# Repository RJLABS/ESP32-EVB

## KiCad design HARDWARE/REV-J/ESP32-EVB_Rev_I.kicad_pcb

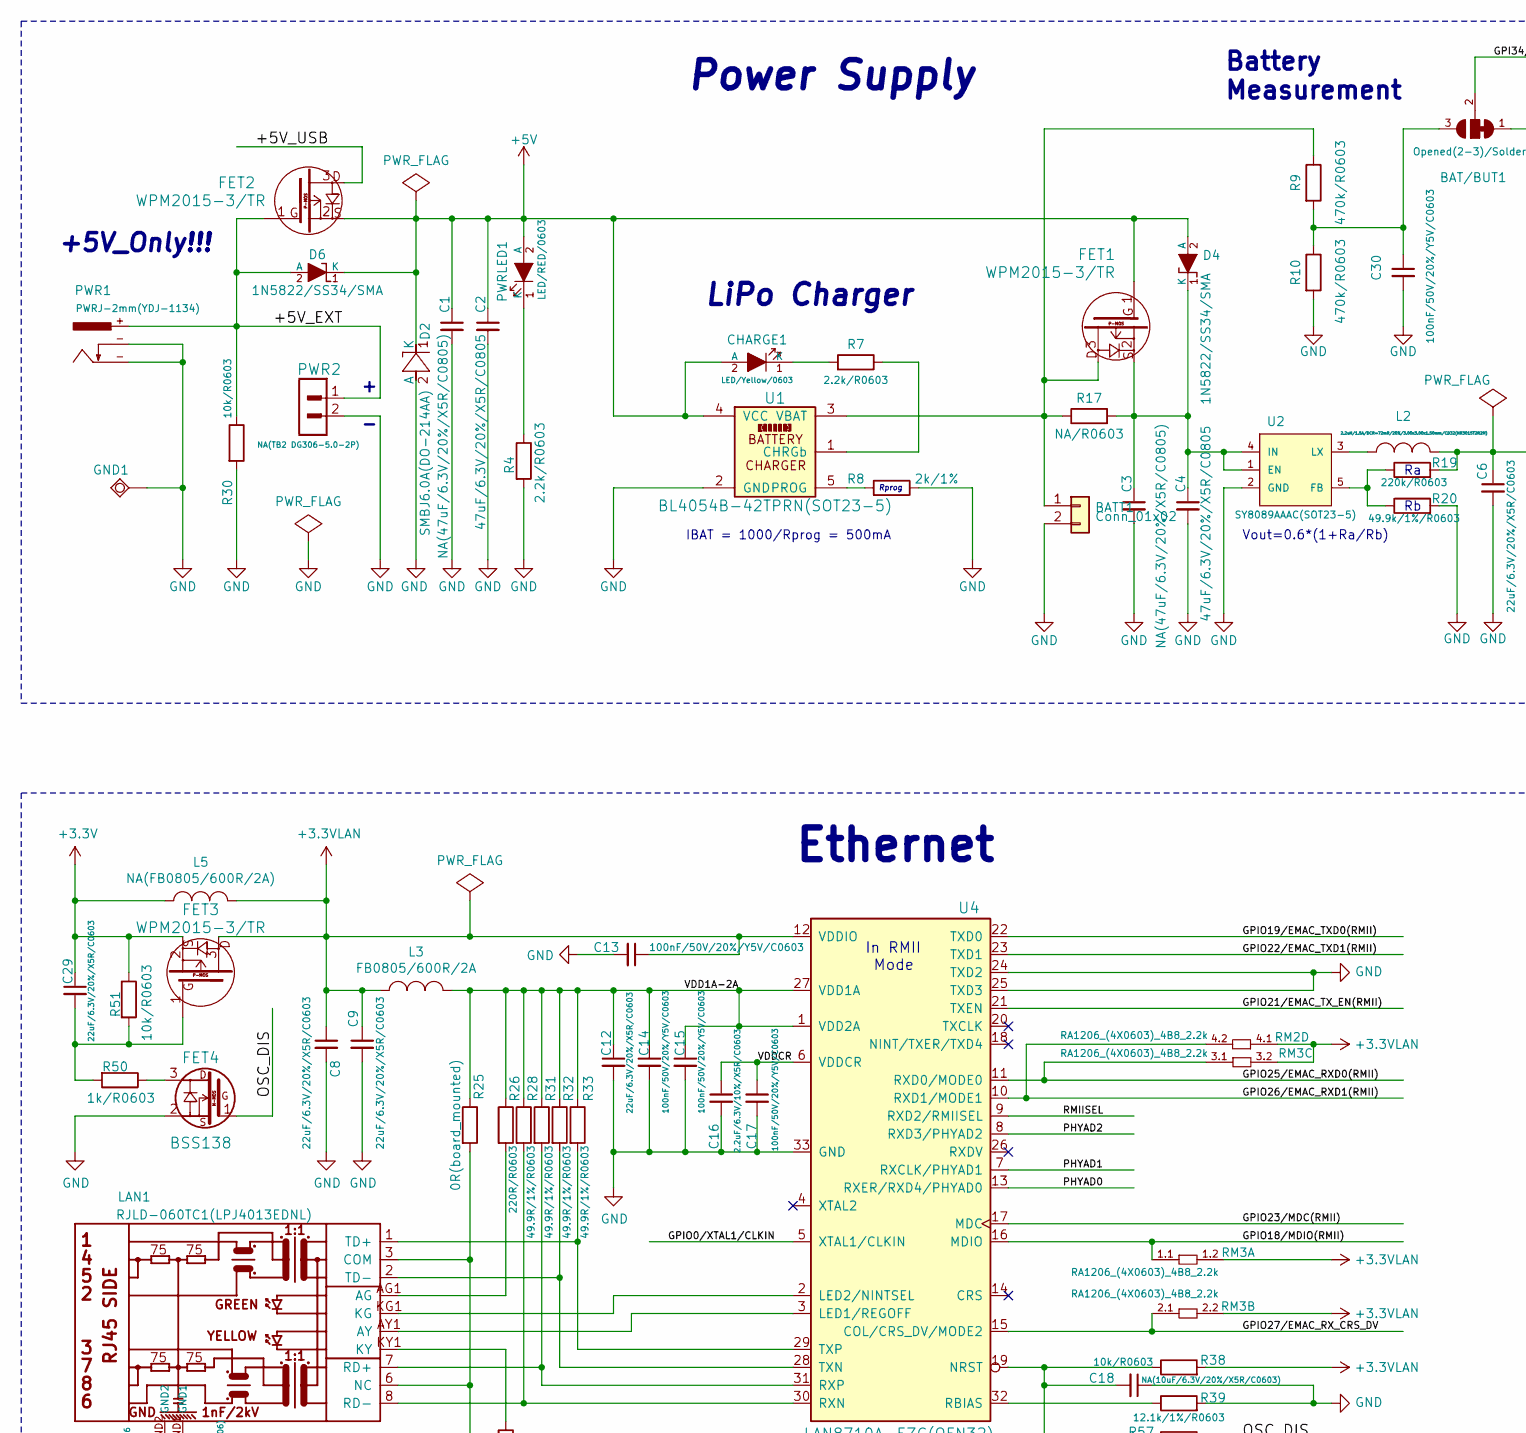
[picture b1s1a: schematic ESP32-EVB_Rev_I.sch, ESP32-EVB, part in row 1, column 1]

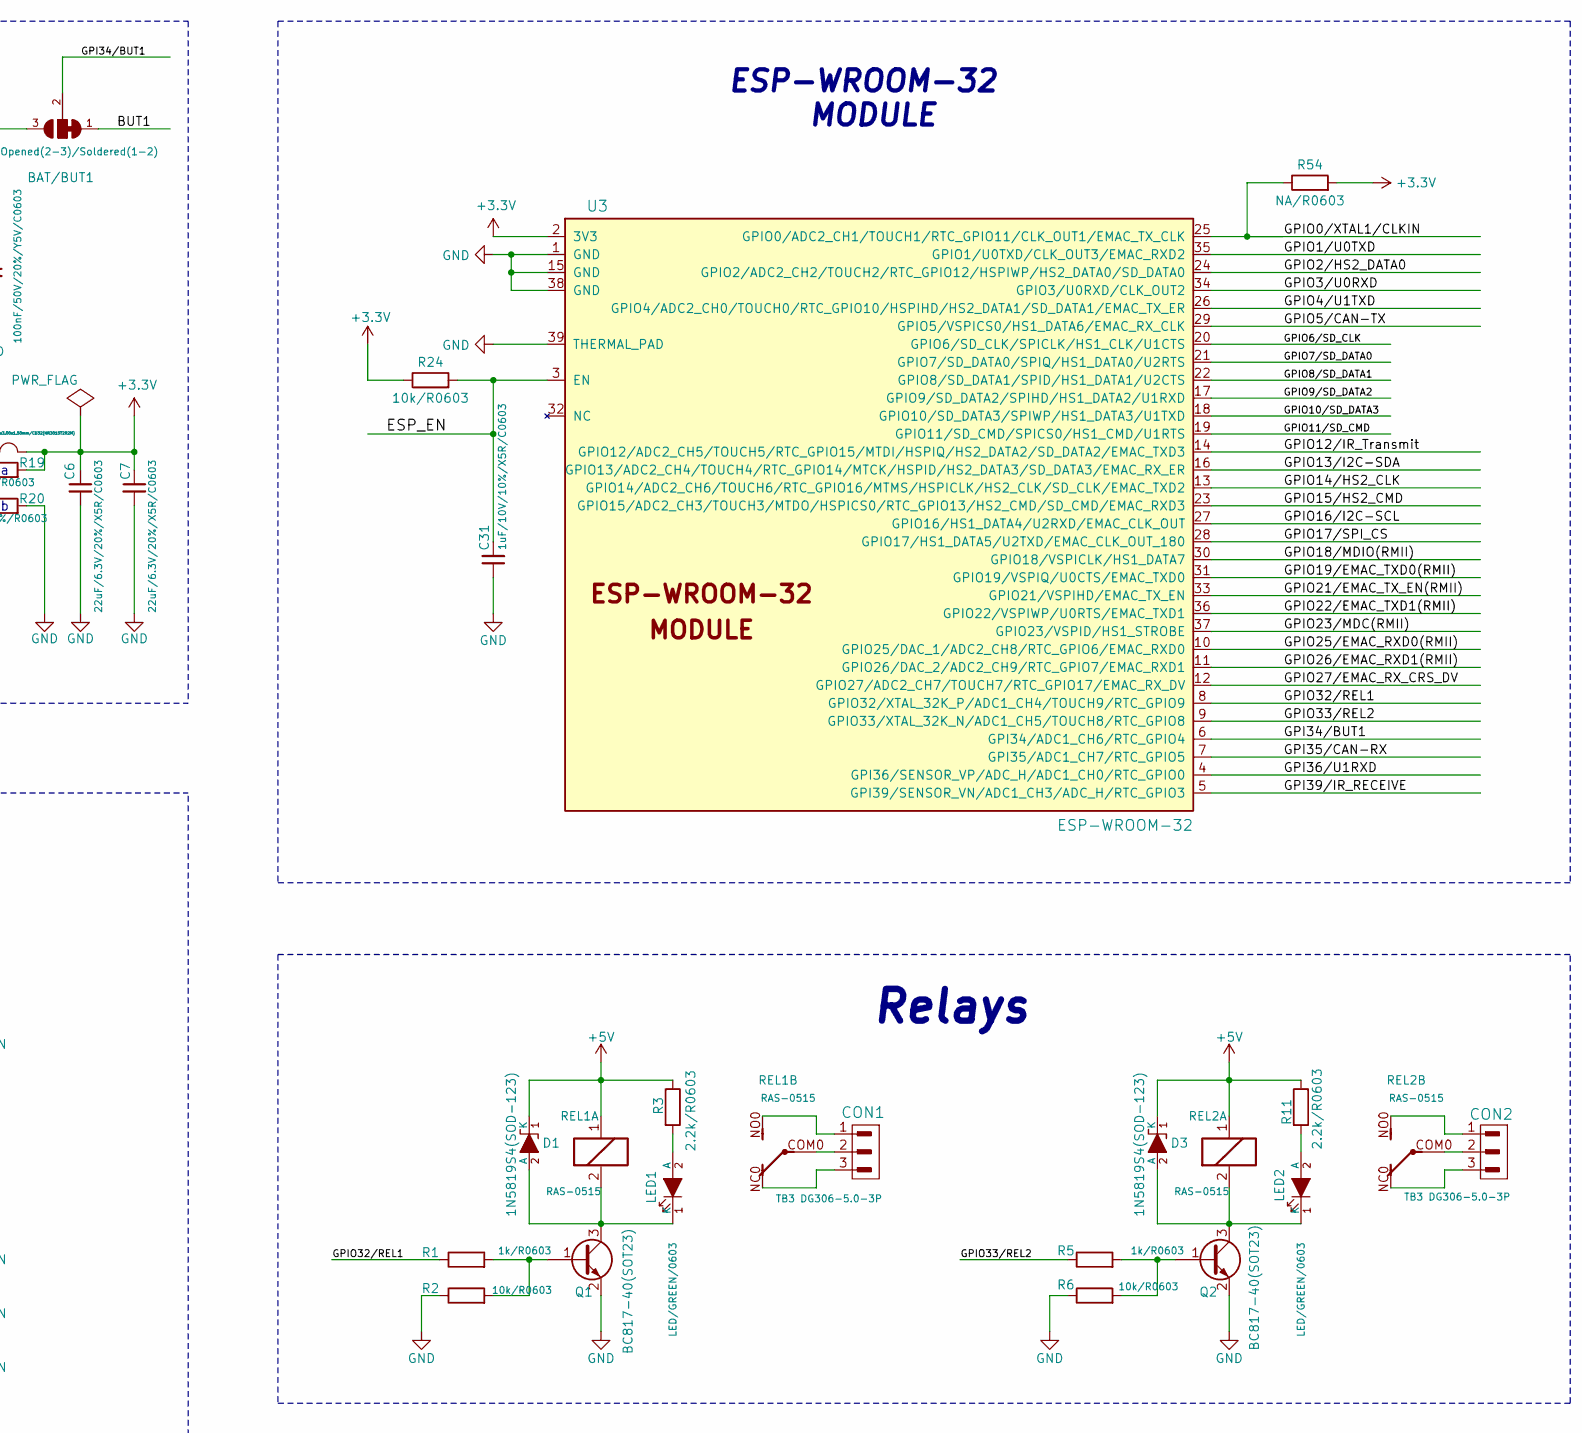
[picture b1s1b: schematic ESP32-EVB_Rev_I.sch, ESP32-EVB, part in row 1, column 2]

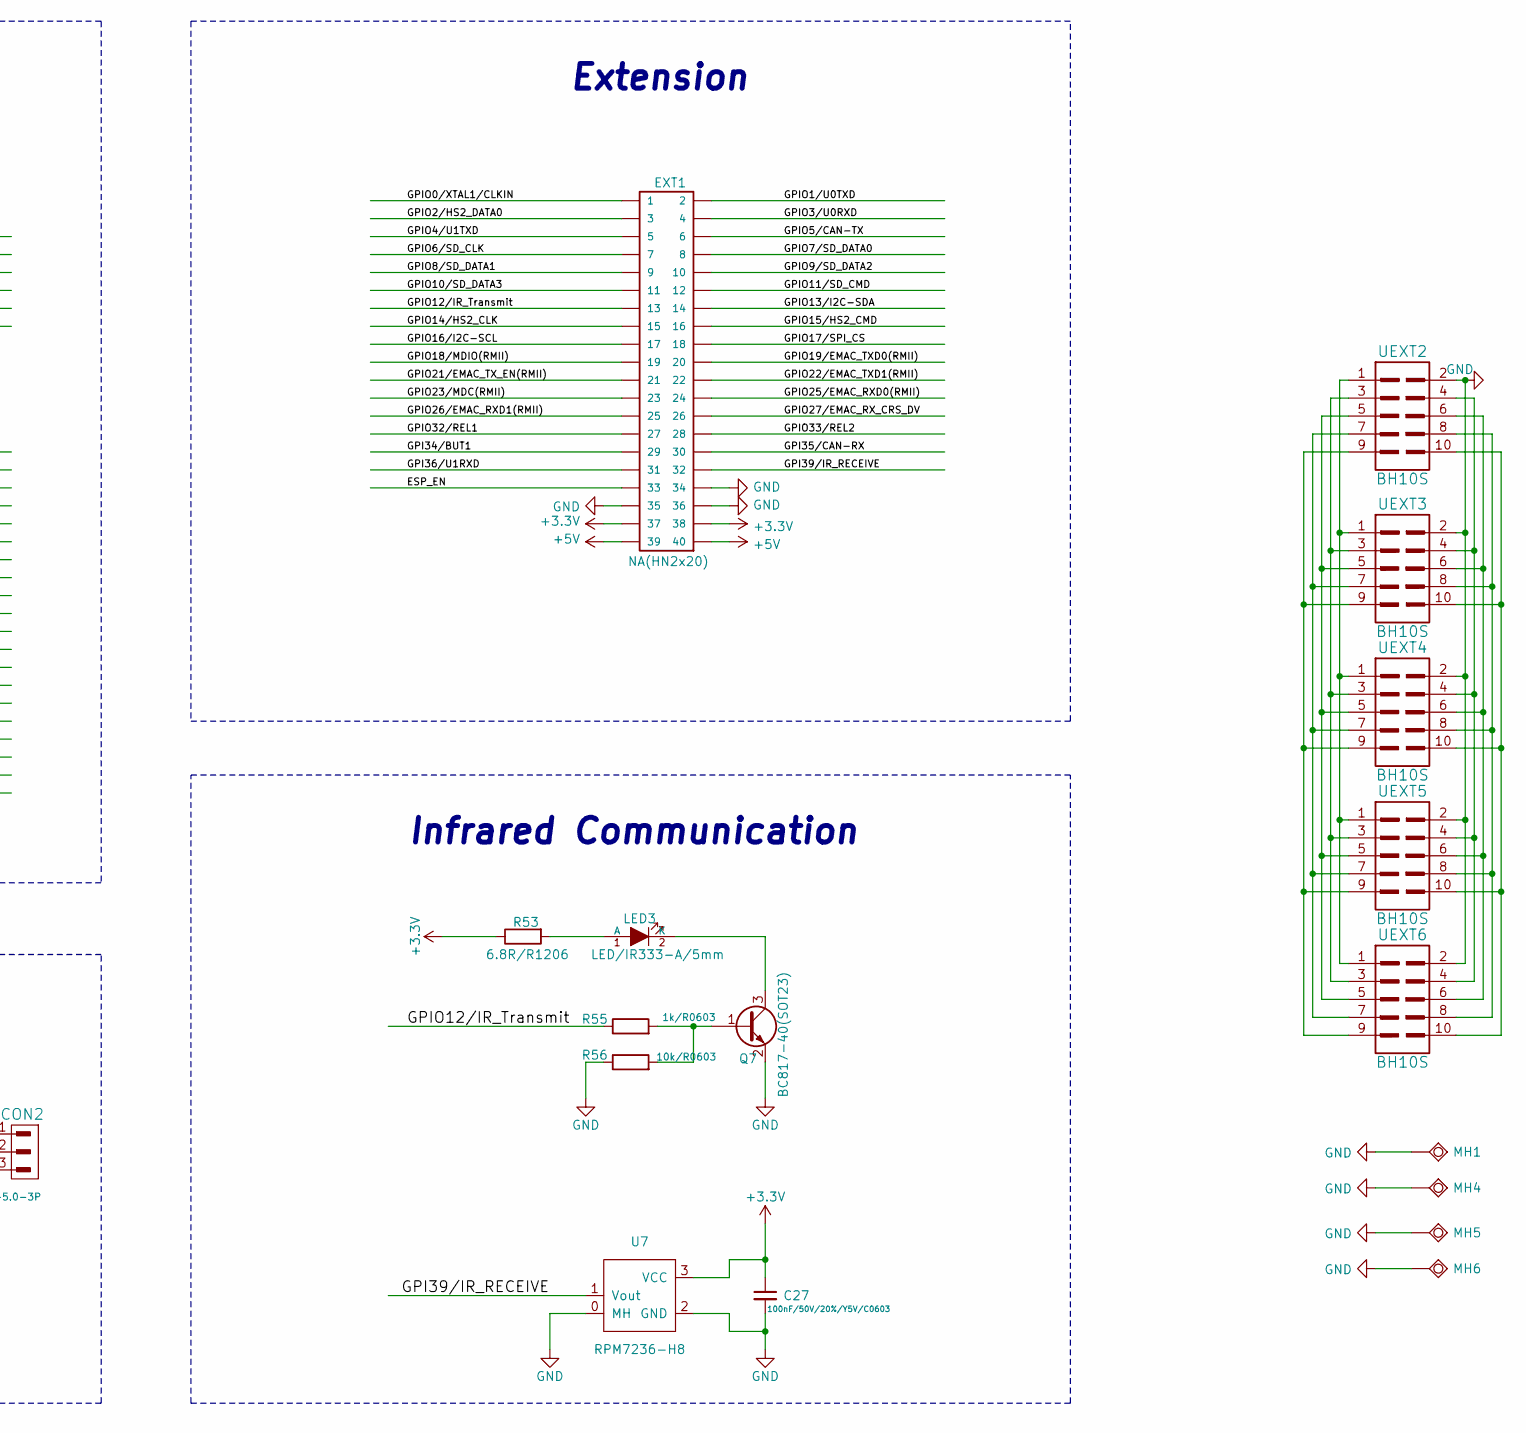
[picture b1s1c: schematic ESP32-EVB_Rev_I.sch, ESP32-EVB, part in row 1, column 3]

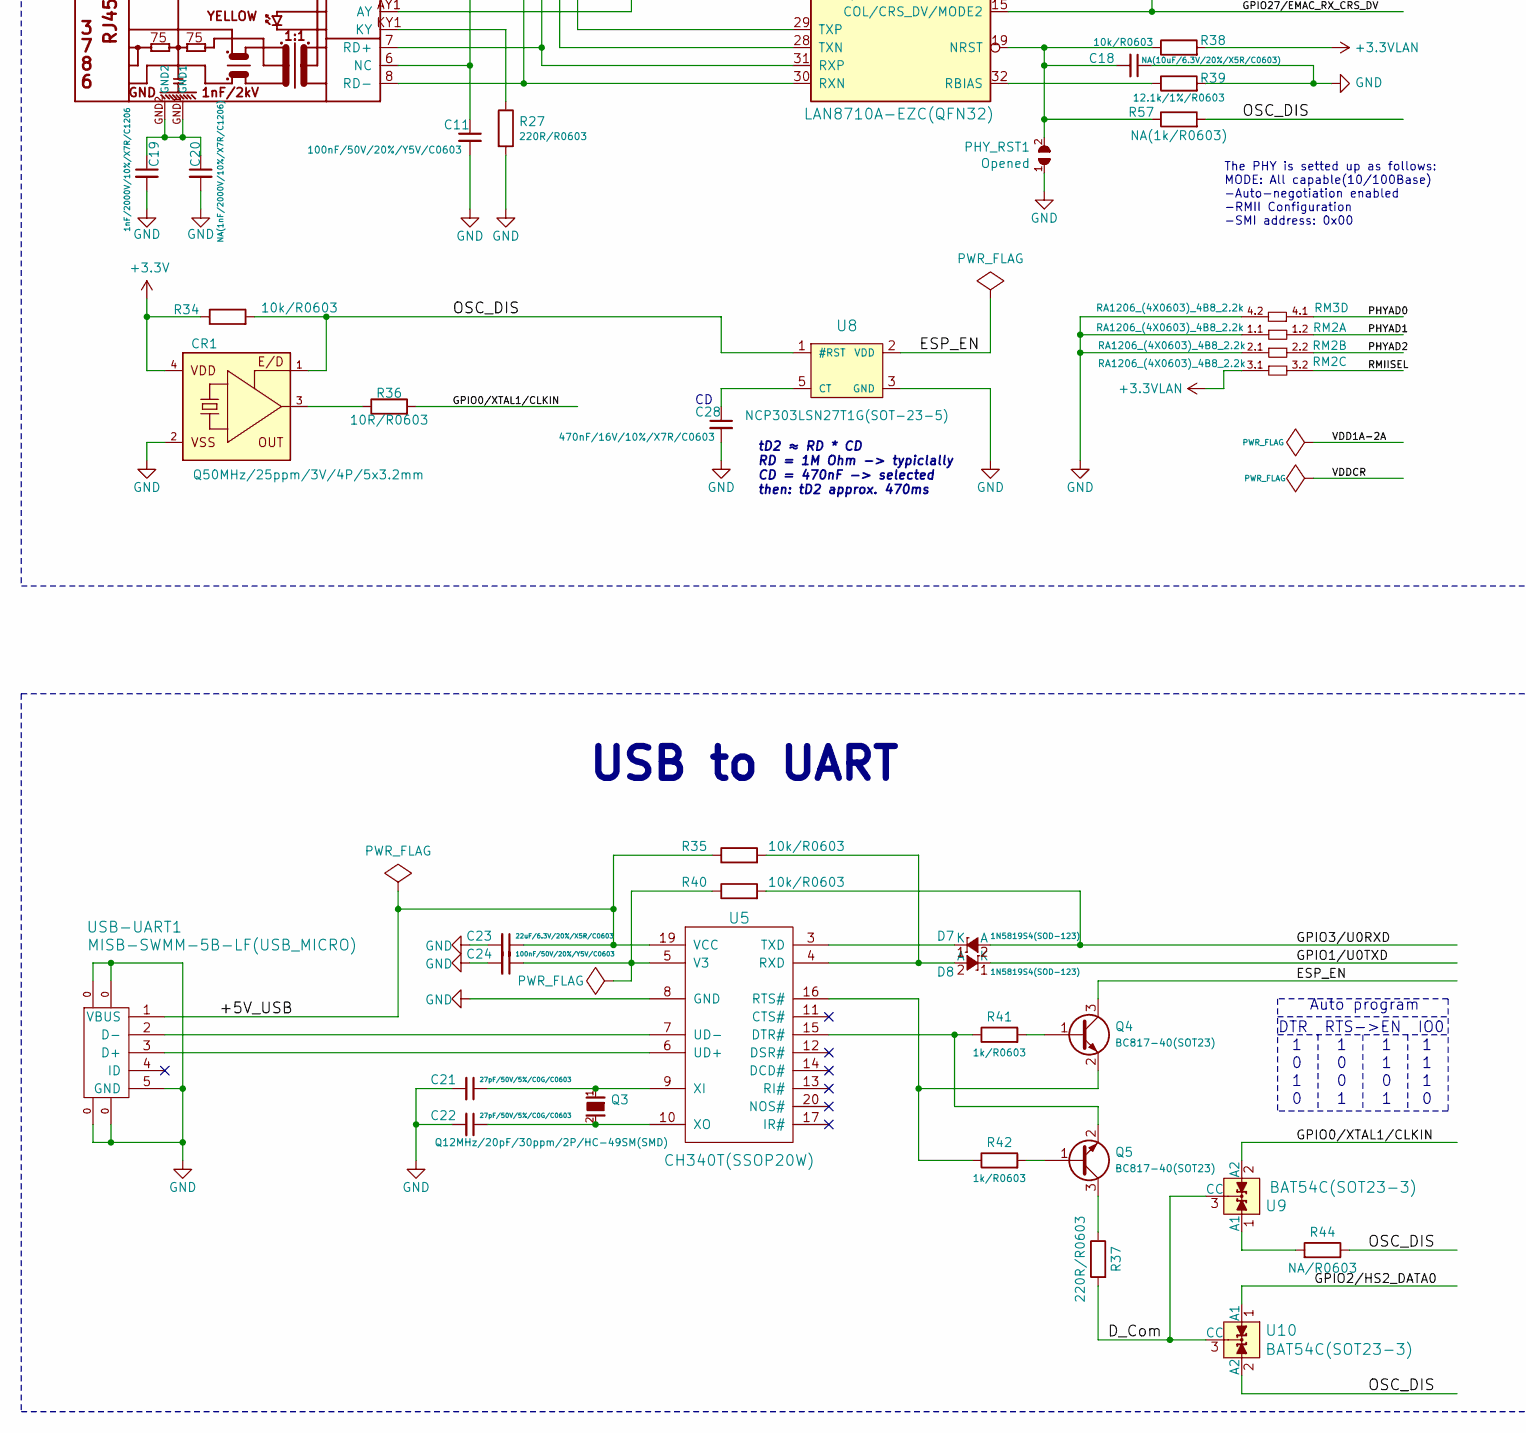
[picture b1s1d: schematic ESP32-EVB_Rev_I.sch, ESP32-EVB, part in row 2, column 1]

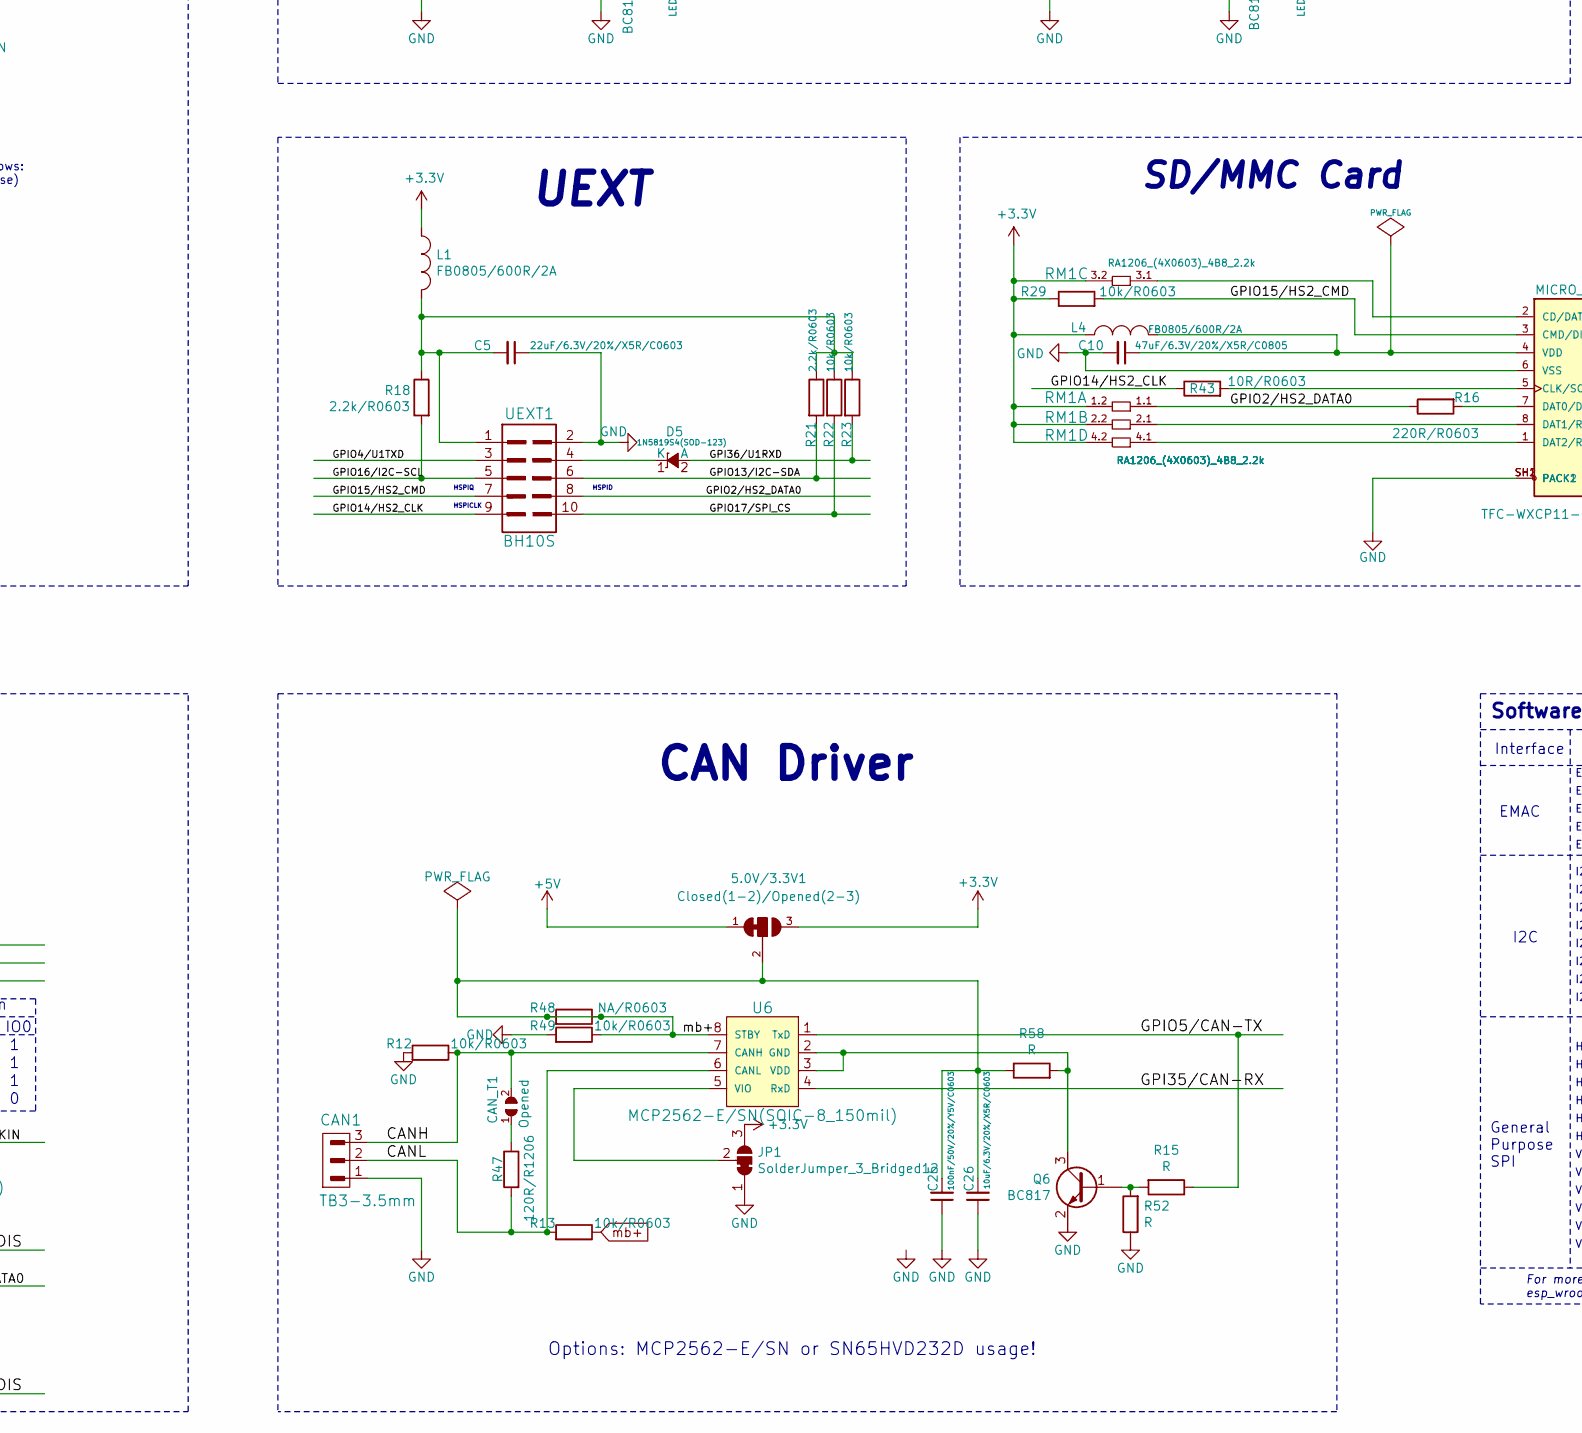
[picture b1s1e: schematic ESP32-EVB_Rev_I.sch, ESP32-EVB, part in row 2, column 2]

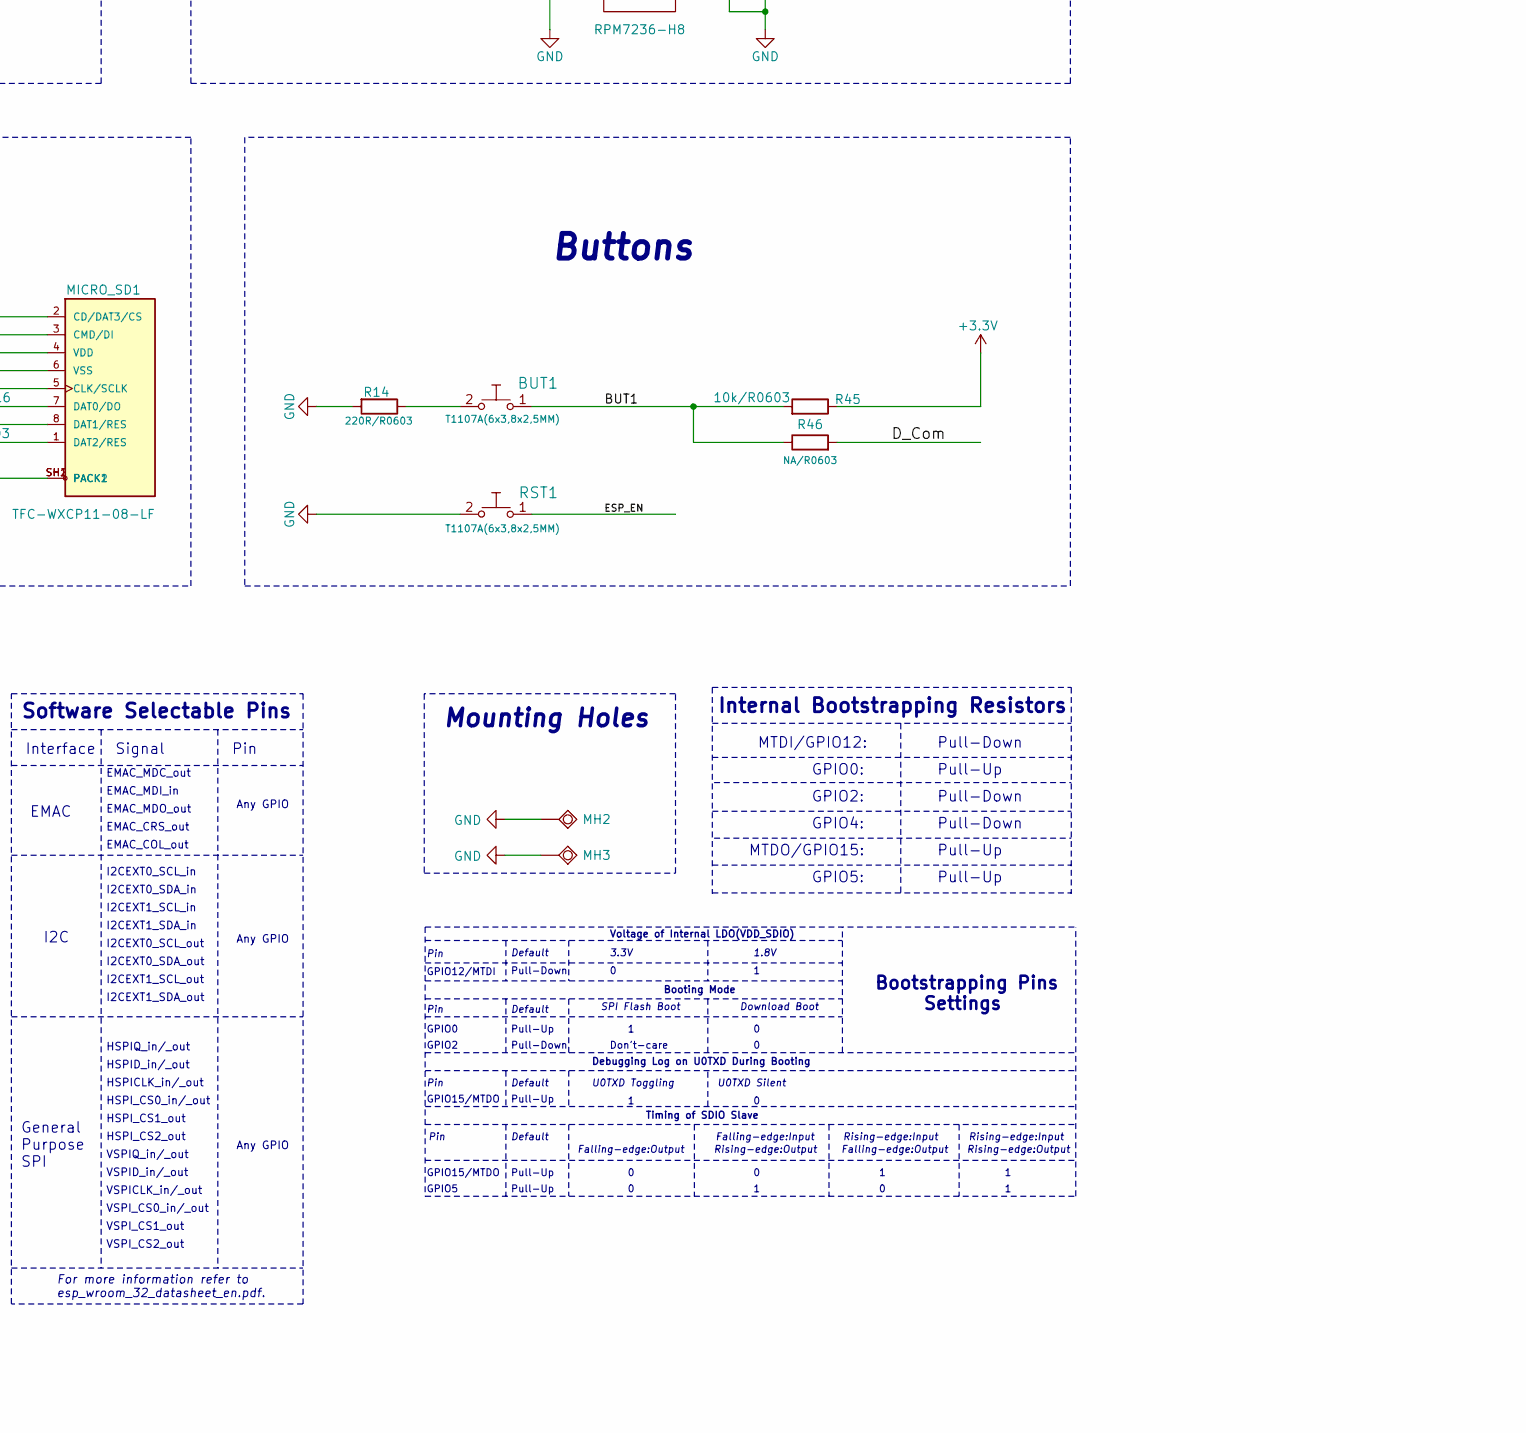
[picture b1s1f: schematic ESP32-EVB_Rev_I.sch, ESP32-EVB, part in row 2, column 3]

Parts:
5.0V/3.3V1: Closed(1-2)/Opened(2-3); SJ_2_SMALL_12_TIED
BAT/BUT1: Opened(2-3)/Soldered(1-2); SJ_2_SMALL
BATT1: Conn_01x02; JST_XH_B2B-XH-AM_1x02_P2.50mm_Vertical
BUT1: T1107A(6x3,8x2,5MM)
C1, C3: NA(47uF/6.3V/20%/X5R/C0805); C_0805_5MIL_DWS
C2, C4, C10: 47uF/6.3V/20%/X5R/C0805; C_0805_5MIL_DWS
C5, C6, C7, C8, C9, C12, C23, C29: 22uF/6.3V/20%/X5R/C0603; C_0603_5MIL_DWS
C11, C13, C14, C15, C17, C24, C25, C27, C30: 100nF/50V/20%/Y5V/C0603; C_0603_5MIL_DWS
C16: 2.2uF/6.3V/10%/X5R/C0603; C_0603_5MIL_DWS
C18: NA(10uF/6.3V/20%/X5R/C0603); C_0603_5MIL_DWS
C19: 1nF/2000V/10%/X7R/C1206; C_1206_5MIL_DWS_ISO
C20: NA(1nF/2000V/10%/X7R/C1206); C_1206_5MIL_DWS_ISO
C21, C22: 27pF/50V/5%/C0G/C0603; C_0603_5MIL_DWS
C26: 10uF/6.3V/20%/X5R/C0603; C_0603_5MIL_DWS
C28: 470nF/16V/10%/X7R/C0603; C_0603_5MIL_DWS
C31: 1uF/10V/10%/X5R/C0603; C_0603_5MIL_DWS
CAN1: TB3-3.5mm
CAN_T1: Opened; SJ
CHARGE1: LED/Yellow/0603; LED_0603_KA
CON1, CON2: TB3 DG306-5.0-3P; TB3-DG306-5.0_3P
CR1: Q50MHz/25ppm/3V/4P/5x3.2mm; 5032-4P_HCX-3S
D1, D3, D5, D7, D8: 1N5819S4(SOD-123); SOD-123_1C-2A_KA
D2: SMBJ6.0A(DO-214AA); DO214AA_1(K)-2(A)
D4, D6: 1N5822/SS34/SMA; SMA-KA
EXT1: NA(HN2x20); HN2x20
FET1, FET2, FET3: WPM2015-3/TR; SOT23
FET4: BSS138; SOT23
GND1: TESTPAD; TESTPAD_40-ROUND
JP1: SolderJumper_3_Bridged12; SolderJumper-3_P1.3mm_Bridged2Bar12_Pad1.0x1.5mm_NumberLabe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
L1, L3, L4: FB0805/600R/2A; L_0805_5MIL_DWS
L2: 2.2uH/1.5A/DCR=72mR/20%/3.00x3.00x1.50mm/CD32(NR3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; CD32
L5: NA(FB0805/600R/2A); L_0805_5MIL_DWS
LAN1: RJLD-060TC1(LPJ4013EDNL); RJLBC-060TC1
LED1, LED2: LED/GREEN/0603; LED_0603_KA
LED3: LED/IR333-A/5mm; LED-5mm-PTH-AK
MH1, MH4, MH5, MH6: Mounting_hole_Shield_3.3mm; MountingHole_3.2mm_M3_Pad_Via
MH2, MH3: Mounting_hole_Shield_3.3mm
MICRO_SD1: TFC-WXCP11-08-LF
PHY_RST1: Opened; SJ
PWR1: PWRJ-2mm(YDJ-1134); PWRJ-2mm(YDJ-1136)
PWR2: NA(TB2 DG306-5.0-2P); TB2-DG306-5.0_2P
PWRLED1: LED/RED/0603; LED_0603_KA
Q1, Q2, Q4, Q5, Q7: BC817-40(SOT23); SOT23
Q3: Q12MHz/20pF/30ppm/2P/HC-49SM(SMD); Q_49U3HMS
Q6: BC817; SOT-23
R1, R5, R41, R42, R50, R55: 1k/R0603; R_0603_5MIL_DWS
R2, R6, R12, R13, R22, R23, R24, R29, R30, R34, R35, R38, R40, R45, R49, R51, R56: 10k/R0603; R_0603_5MIL_DWS
R3, R4, R7, R11, R18, R21: 2.2k/R0603; R_0603_5MIL_DWS
R8: 2k/1%; R_0603_5MIL_DWS
R9, R10: 470k/R0603; R_0603_5MIL_DWS
R14, R16, R26, R27, R37: 220R/R0603; R_0603_5MIL_DWS
R15, R52, R58: R; R_0603_1608Metric
R17, R44, R46, R48, R54: NA/R0603; R_0603_5MIL_DWS
R19: 220k/R0603; R_0603_5MIL_DWS
R20: 49.9k/1%/R0603; R_0603_5MIL_DWS
R25: 0R(board_mounted); 0R_0603
R28, R31, R32, R33: 49.9R/1%/R0603; R_0603_5MIL_DWS
R36, R43: 10R/R0603; R_0603_5MIL_DWS
R39: 12.1k/1%/R0603; R_0603_5MIL_DWS
R47: 120R/R1206; R_1206_5MIL_DWS
R53: 6.8R/R1206; R_1206_5MIL_DWS
R57: NA(1k/R0603); R_0603_5MIL_DWS
REL1, REL2: RAS-0515; Relay_RAS-05-15
RM1, RM2, RM3: RA1206_(4X0603)_4B8_2.2k; R_MATRIX_4
RST1: T1107A(6x3,8x2,5MM)
U1: BL4054B-42TPRN(SOT23-5); SOT-23-5
U2: SY8089AAAC(SOT23-5); SOT-23-5
U3: ESP-WROOM-32; ESP-WROOM-32_MODULE
U4: LAN8710A-EZC(QFN32); QFN32_EP(33)_5.00x5.00x0.90mm_Pitch_0.50mm
U5: CH340T(SSOP20W); SSOP-20W
U6: MCP2562-E/SN(SOIC-8_150mil); SOIC-8_150mil
U7: RPM7236-H8
U8: NCP303LSN27T1G(SOT-23-5); SOT-23-5
U9, U10: BAT54C(SOT23-3); SOT23-3
UEXT1: BH10S; UEXT_ML10
UEXT2, UEXT3, UEXT4, UEXT5, UEXT6: BH10S; IDC-Header_2x05_P2.54mm_Vertical
USB-UART1: MISB-SWMM-5B-LF(USB_MICRO); USB-MICRO_MISB-SWMM-5B_LF

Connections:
+3.3VLAN: C8.1, C9.1, C13.1, FET3.3, L3.1, L5.2, R38.2, RM2.3.1, RM2.4.1, RM3.1.2, RM3.2.2, RM3.3.2, U4.12 (VDDIO)
+3V3: 5.0V/3.3V1.3, C6.1, C7.1, C27.1, C29.1, CR1.4 (VDD), EXT1.37, EXT1.38, FET3.2, JP1.3 (B), L1.1, L2.2, L4.1, L5.1, R19.2, R24.1, R29.1, R34.1, R45.1, R51.1, R53.1, R54.2, RM1.1.2, RM1.2.2, RM1.3.2, RM1.4.2, U3.2 (3V3), U7.3 (VCC)
+5V: 5.0V/3.3V1.1, C1.1, C2.1, CHARGE1.2 (A), D1.1 (K), D2.1 (K), D3.1 (K), D4.2 (A), D6.1 (K), EXT1.39, EXT1.40, FET1.1, FET2.2, PWRLED1.2 (A), R3.1, R11.1, REL1.1, REL2.1, U1.4 (VCC)
/+5V_EXT: D6.2 (A), FET2.1, PWR1.+, PWR2.1, R30.1
/+5V_USB: C23.1, FET2.3, R35.1, U5.19 (VCC), USB-UART1.1 (VBUS)
/BUT1: BAT/BUT1.1, BUT1.1, R45.2, R46.1
/CANH: CAN1.3, CAN_T1.2, R12.1, U6.7 (CANH)
/CANL: CAN1.2, R13.2, R47.2, U6.6 (CANL)
/D_Com: R37.2, R46.2, U9.3 (CC), U10.3 (CC)
/ESP_EN: C31.2, EXT1.33, Q4.3 (C), R24.2, RST1.1, U3.3 (EN), U8.2 (VDD)
/GPI34/BUT1: BAT/BUT1.2, EXT1.29, U3.6 (GPI34/ADC1_CH6/RTC_GPIO4)
/GPI35/CAN-RX: EXT1.30, U3.7 (GPI35/ADC1_CH7/RTC_GPIO5), U6.4 (RxD)
/GPI36/U1RXD: D5.2 (A), EXT1.31, R23.2, U3.4 (GPI36/SENSOR_VP/ADC_H/ADC1_CH0/RTC_GPIO0)
/GPI39/IR_RECEIVE: EXT1.32, U3.5 (GPI39/SENSOR_VN/ADC1_CH3/ADC_H/RTC_GPIO3), U7.1 (Vout)
/GPIO0/XTAL1/CLKIN: EXT1.1, R36.2, R54.1, U3.25 (GPIO0/ADC2_CH1/TOUCH1/RTC_GPIO11/CLK_OU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), U4.5 (XTAL1/CLKIN), U9.2 (A2)
/GPIO1/U0TXD: D8.1 (K), EXT1.2, U3.35 (GPIO1/U0TXD/CLK_OUT3/EMAC_RXD2)
/GPIO2/HS2_DATA0: EXT1.3, R16.1, RM1.1.1, U3.24 (GPIO2/ADC2_CH2/TOUCH2/RTC_GPIO12/HSPIWP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), U10.1 (A1), UEXT1.8
/GPIO3/U0RXD: D7.2 (A), EXT1.4, R40.2, U3.34 (GPIO3/U0RXD/CLK_OUT2)
/GPIO4/U1TXD: EXT1.5, U3.26 (GPIO4/ADC2_CH0/TOUCH0/RTC_GPIO10/HSPIHD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), UEXT1.3
/GPIO5/CAN-TX: EXT1.6, R15.1, U3.29 (GPIO5/VSPICS0/HS1_DATA6/EMAC_RX_CLK), U6.1 (TxD)
/GPIO6/SD_CLK: EXT1.7, U3.20 (GPIO6/SD_CLK/SPICLK/HS1_CLK/U1CTS)
/GPIO7/SD_DATA0: EXT1.8, U3.21 (GPIO7/SD_DATA0/SPIQ/HS1_DATA0/U2RTS)
/GPIO8/SD_DATA1: EXT1.9, U3.22 (GPIO8/SD_DATA1/SPID/HS1_DATA1/U2CTS)
/GPIO9/SD_DATA2: EXT1.10, U3.17 (GPIO9/SD_DATA2/SPIHD/HS1_DATA2/U1RXD)
/GPIO10/SD_DATA3: EXT1.11, U3.18 (GPIO10/SD_DATA3/SPIWP/HS1_DATA3/U1TXD)
/GPIO11/SD_CMD: EXT1.12, U3.19 (GPIO11/SD_CMD/SPICS0/HS1_CMD/U1RTS)
/GPIO12/IR_Transmit: EXT1.13, R55.1, U3.14 (GPIO12/ADC2_CH5/TOUCH5/RTC_GPIO15/MTDI/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)
/GPIO13/I2C-SDA: EXT1.14, R21.2, U3.16 (GPIO13/ADC2_CH4/TOUCH4/RTC_GPIO14/MTCK/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), UEXT1.6
/GPIO14/HS2_CLK: EXT1.15, R43.1, U3.13 (GPIO14/ADC2_CH6/TOUCH6/RTC_GPIO16/MTMS/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), UEXT1.9
/GPIO15/HS2_CMD: EXT1.16, MICRO_SD1.3 (CMD/DI), R29.2, U3.23 (GPIO15/ADC2_CH3/TOUCH3/MTDO/HSPICS0/RTC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), UEXT1.7
/GPIO16/I2C-SCL: EXT1.17, R18.2, U3.27 (GPIO16/HS1_DATA4/U2RXD/EMAC_CLK_OUT), UEXT1.5
/GPIO17/SPI_CS: EXT1.18, R22.2, U3.28 (GPIO17/HS1_DATA5/U2TXD/EMAC_CLK_OUT_180), UEXT1.10
/GPIO18/MDIO(RMII): EXT1.19, RM3.1.1, U3.30 (GPIO18/VSPICLK/HS1_DATA7), U4.16 (MDIO)
/GPIO19/EMAC_TXD0(RMII): EXT1.20, U3.31 (GPIO19/VSPIQ/U0CTS/EMAC_TXD0), U4.22 (TXD0)
/GPIO21/EMAC_TX_EN(RMII): EXT1.21, U3.33 (GPIO21/VSPIHD/EMAC_TX_EN), U4.21 (TXEN)
/GPIO22/EMAC_TXD1(RMII): EXT1.22, U3.36 (GPIO22/VSPIWP/U0RTS/EMAC_TXD1), U4.23 (TXD1)
/GPIO23/MDC(RMII): EXT1.23, U3.37 (GPIO23/VSPID/HS1_STROBE), U4.17 (MDC)
/GPIO25/EMAC_RXD0(RMII): EXT1.24, RM3.3.1, U3.10 (GPIO25/DAC_1/ADC2_CH8/RTC_GPIO6/EMAC_RX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), U4.11 (RXD0/MODE0)
/GPIO26/EMAC_RXD1(RMII): EXT1.25, RM2.4.2, U3.11 (GPIO26/DAC_2/ADC2_CH9/RTC_GPIO7/EMAC_RX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), U4.10 (RXD1/MODE1)
/GPIO27/EMAC_RX_CRS_DV: EXT1.26, RM3.2.1, U3.12 (GPIO27/ADC2_CH7/TOUCH7/RTC_GPIO17/EMAC_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), U4.15 (COL/CRS_DV/MODE2)
/GPIO32/REL1: EXT1.27, R1.1, U3.8 (GPIO32/XTAL_32K_P/ADC1_CH4/TOUCH9/RTC_G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)
/GPIO33/REL2: EXT1.28, R5.1, U3.9 (GPIO33/XTAL_32K_N/ADC1_CH5/TOUCH8/RTC_G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)
/OSC_DIS: CR1.1 (E/D), FET4.1 (G), R34.2, R44.1, R57.2, U8.1 (#RST), U10.2 (A2)
/PHYAD0: RM3.4.1, U4.13 (RXER/RXD4/PHYAD0)
/PHYAD1: RM2.1.2, U4.7 (RXCLK/PHYAD1)
/PHYAD2: RM2.2.2, U4.8 (RXD3/PHYAD2)
/RMIISEL: RM2.3.2, U4.9 (RXD2/RMIISEL)
/VDD1A-2A: C12.1, C14.1, C15.1, L3.2, R25.1, R26.1, R28.1, R31.1, R32.1, R33.1, U4.1 (VDD2A), U4.27 (VDD1A)
/VDDCR: C16.1, C17.1, U4.6 (VDDCR)
GND: BATT1.2, C1.2, C2.2, C3.2, C4.2, C5.1, C6.2, C7.2, C8.2, C9.2, C10.2, C11.2, C12.2, C13.2, C14.2, C15.2, C16.2, C17.2, C18.1, C19.2, C20.2, C21.2, C22.2, C23.2, C24.2, C25.1, C26.1, C27.2, C28.2, C30.2, C31.1, CAN1.1, CR1.2 (VSS), D2.2 (A), EXT1.34, EXT1.35, EXT1.36, FET4.2 (S), GND1.1, JP1.1 (A), MH1.GND1, MH2.GND1, MH3.GND1, MH4.GND1, MH5.GND1, MH6.GND1, MICRO_SD1.6 (VSS), MICRO_SD1.SH1 (PACK1), MICRO_SD1.SH2 (PACK2), PHY_RST1.1, PWR1.-, PWR2.2, Q1.2 (E), Q2.2 (E), Q6.2 (E), Q7.2 (E), R2.1, R4.2, R6.1, R8.1, R10.2, R12.2, R14.2, R20.2, R27.2, R30.2, R39.2, R49.2, R52.1, R56.1, RM2.1.1, RM2.2.1, RM3.4.2, RST1.2, U1.2 (GND), U2.2 (GND), U3.1 (GND), U3.15 (GND), U3.38 (GND), U3.39 (THERMAL_PAD), U4.24 (TXD2), U4.25 (TXD3), U4.33 (GND), U5.8 (GND), U7.0 (MH), U7.2 (GND), U8.3 (GND), UEXT1.2, UEXT2.2, UEXT3.2, UEXT4.2, UEXT5.2, UEXT6.2, USB-UART1.0, USB-UART1.5 (GND)
unnamed: BAT/BUT1.3, C30.1, R9.2, R10.1
unnamed: BATT1.1, FET1.3, R9.1, R17.1, U1.3 (VBAT)
unnamed: BUT1.2, R14.1
unnamed: C3.1, C4.1, D4.1 (K), FET1.2, R17.2, U2.1 (EN), U2.4 (IN)
unnamed: C5.2, L1.2, R18.1, R21.1, R22.1, R23.1, UEXT1.1
unnamed: C10.1, L4.2, MICRO_SD1.4 (VDD)
unnamed: C11.1, LAN1.3 (COM), LAN1.6 (NC), R25.2
unnamed: C18.2, PHY_RST1.2, R38.1, R57.1, U4.19 (NRST)
unnamed: C19.1, C20.1, LAN1.GND1, LAN1.GND2
unnamed: C21.1, Q3.1, U5.9 (XI)
unnamed: C22.1, Q3.2, U5.10 (XO)
unnamed: C24.1, R40.1, U5.5 (V3)
unnamed: C28.1, U8.5 (CT)
unnamed: C29.2, FET3.1, R50.2, R51.2
unnamed: CAN_T1.1, R47.1
unnamed: CHARGE1.1 (K), R7.2
unnamed: CON1.1, REL1.NO0
unnamed: CON1.2, REL1.COM0
unnamed: CON1.3, REL1.NC0
unnamed: CON2.1, REL2.NO0
unnamed: CON2.2, REL2.COM0
unnamed: CON2.3, REL2.NC0
unnamed: CR1.3 (OUT), R36.1
unnamed: D1.2 (A), LED1.1 (K), Q1.3 (C), REL1.2
unnamed: D3.2 (A), LED2.1 (K), Q2.3 (C), REL2.2
unnamed: D5.1 (K), UEXT1.4
unnamed: D7.1 (K), U5.3 (TXD)
unnamed: D8.2 (A), R35.2, U5.4 (RXD)
unnamed: FET4.3 (D), R50.1
unnamed: JP1.2 (C), U6.5 (VIO)
unnamed: L2.1, U2.3 (LX)
unnamed: LAN1.1 (TD+), R33.2, U4.29 (TXP)
unnamed: LAN1.2 (TD-), R32.2, U4.28 (TXN)
unnamed: LAN1.7 (RD+), R31.2, U4.31 (RXP)
unnamed: LAN1.8 (RD-), R28.2, U4.30 (RXN)
unnamed: LAN1.AG1 (AG), R26.2
unnamed: LAN1.AY1 (AY), U4.3 (LED1/REGOFF)
unnamed: LAN1.KG1 (KG), U4.2 (LED2/NINTSEL)
unnamed: LAN1.KY1 (KY), R27.1
unnamed: LED1.2 (A), R3.2
unnamed: LED2.2 (A), R11.2
unnamed: LED3.1 (A), R53.2
unnamed: LED3.2 (K), Q7.3 (C)
unnamed: MICRO_SD1.1 (DAT2/RES), RM1.4.1
unnamed: MICRO_SD1.2 (CD/DAT3/CS), RM1.3.1
unnamed: MICRO_SD1.5 (CLK/SCLK), R43.2
unnamed: MICRO_SD1.7 (DAT0/DO), R16.2
unnamed: MICRO_SD1.8 (DAT1/RES), RM1.2.1
unnamed: PWRLED1.1 (K), R4.1
unnamed: Q1.1 (B), R1.2, R2.2
unnamed: Q2.1 (B), R5.2, R6.2
unnamed: Q4.1 (B), R41.2
unnamed: Q4.2 (E), R42.1, U5.16 (RTS#)
unnamed: Q5.1 (B), R42.2
unnamed: Q5.2 (E), R41.1, U5.15 (DTR#)
unnamed: Q5.3 (C), R37.1
unnamed: Q6.1 (B), R15.2, R52.2
unnamed: Q6.3 (C), R58.2, U6.2 (GND), U6.3 (VDD)
unnamed: Q7.1 (B), R55.2, R56.2
unnamed: R7.1, U1.1 (CHRGb)
unnamed: R8.2, U1.5 (PROG)
unnamed: R19.1, R20.1, U2.5 (FB)
unnamed: R39.1, U4.32 (RBIAS)
unnamed: R44.2, U9.1 (A1)
unnamed: U5.6 (UD+), USB-UART1.3 (D+)
unnamed: U5.7 (UD-), USB-UART1.2 (D-)
unnamed: UEXT2.1, UEXT3.1, UEXT4.1, UEXT5.1, UEXT6.1
unnamed: UEXT2.3, UEXT3.3, UEXT4.3, UEXT5.3, UEXT6.3
unnamed: UEXT2.4, UEXT3.4, UEXT4.4, UEXT5.4, UEXT6.4
unnamed: UEXT2.5, UEXT3.5, UEXT4.5, UEXT5.5, UEXT6.5
unnamed: UEXT2.6, UEXT3.6, UEXT4.6, UEXT5.6, UEXT6.6
unnamed: UEXT2.7, UEXT3.7, UEXT4.7, UEXT5.7, UEXT6.7
unnamed: UEXT2.8, UEXT3.8, UEXT4.8, UEXT5.8, UEXT6.8
unnamed: UEXT2.9, UEXT3.9, UEXT4.9, UEXT5.9, UEXT6.9
unnamed: UEXT2.10, UEXT3.10, UEXT4.10, UEXT5.10, UEXT6.10
mb+: 5.0V/3.3V1.2, C25.2, C26.2, R13.1, R48.1, R48.2, R49.1, R58.1, U6.8 (STBY)

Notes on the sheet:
Vout=0.6*(1+Ra/Rb)
Power Supply
Buttons
Relays
UEXT
In RMII Mode
Ethernet
ESP-WROOM-32 MODULE
SD/MMC Card
Bootstrapping Pins Settings
Internal Bootstrapping Resistors
MTDI/GPIO12:
Pull-Down
GPIO0:
Pull-Up
GPIO2:
GPIO4:
MTDO/GPIO15:
GPIO5:
Voltage of Internal LDO(VDD_SDIO)
Pin
Default
3.3V
1.8V
Booting Mode
GPIO12/MTDI
GPIO0
GPIO2
SPI Flash Boot
Download Boot
Don't-care
Debugging Log on U0TXD During Booting
U0TXD Toggling
U0TXD Silent
GPIO15/MTDO
Timing of SDIO Slave
Falling-edge:Output
Falling-edge:Input
Rising-edge:Output
Rising-edge:Input

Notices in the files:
HARDWARE/REV-J/ESP32-EVB_Rev_I.kicad_pcb:
(C) 2020
